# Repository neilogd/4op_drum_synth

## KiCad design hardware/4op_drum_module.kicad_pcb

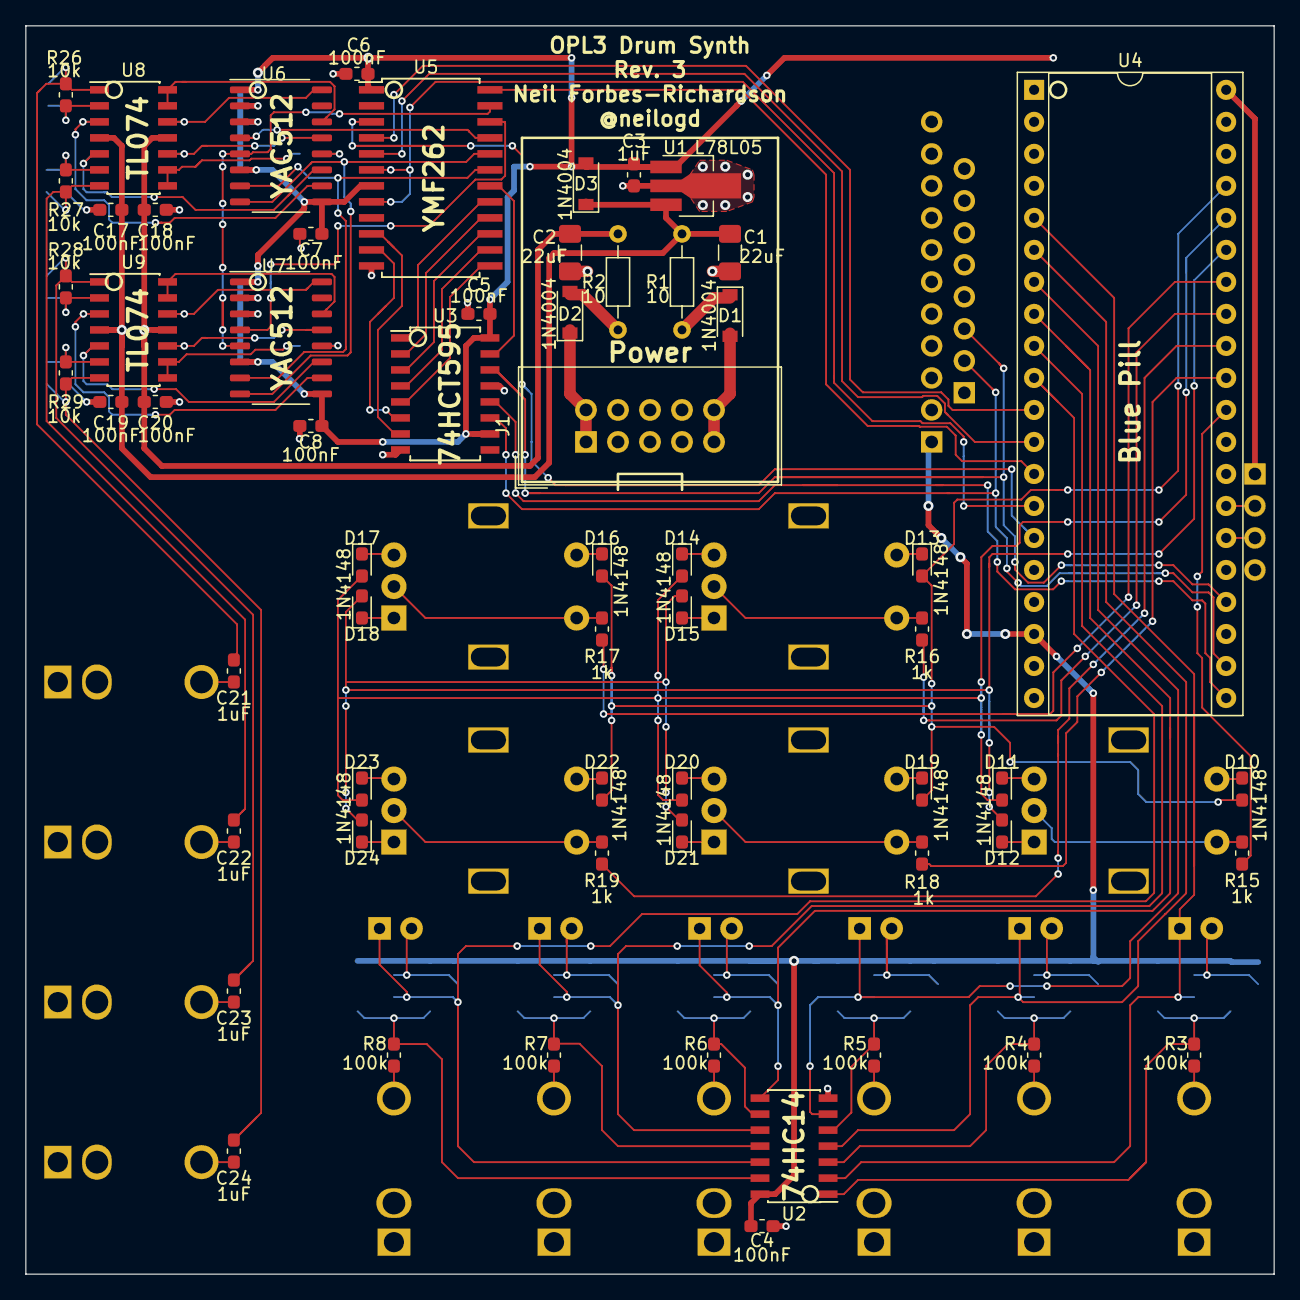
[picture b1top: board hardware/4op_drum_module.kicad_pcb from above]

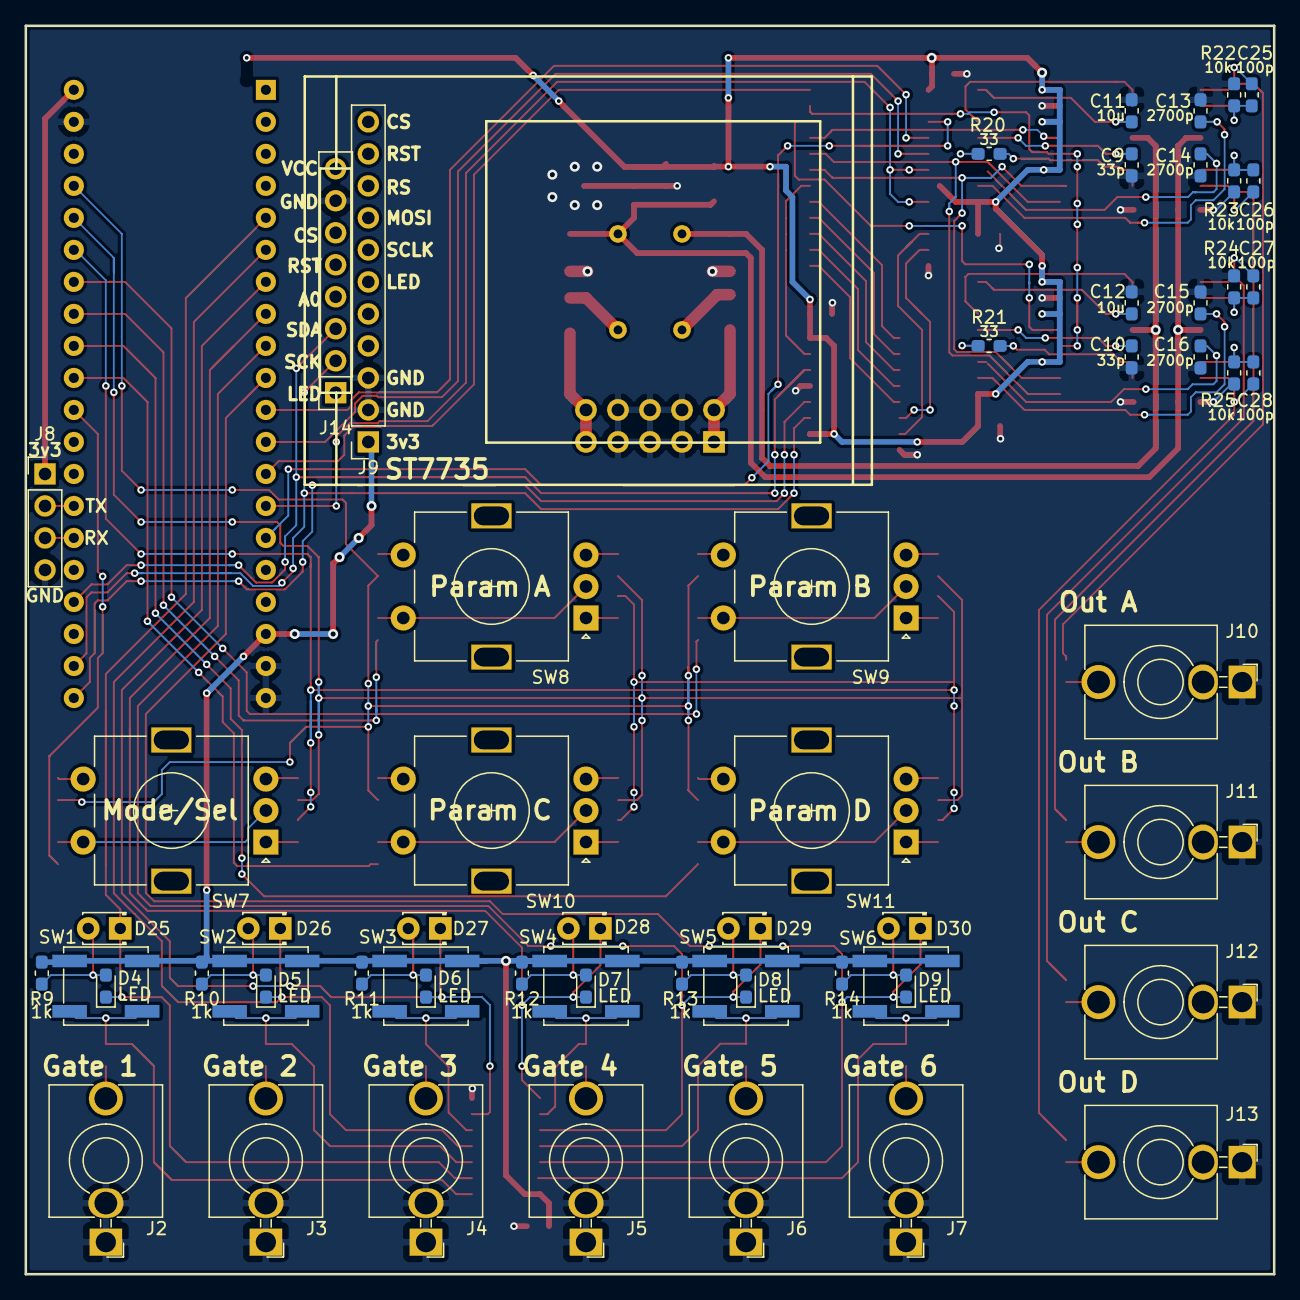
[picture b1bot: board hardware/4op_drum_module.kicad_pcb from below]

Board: 2 copper layers, 99.1 x 99.1 mm, 121 parts (60 on the bottom side), 113 nets.

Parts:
C1, C2: 22uF; C_1206_3216Metric_Pad1.42x1.75mm_HandSolder
C3, C21, C22, C23, C24: 1uF; C_0603_1608Metric_Pad1.05x0.95mm_HandSolder
C4, C5, C6, C7, C8, C17, C18, C19, C20: 100nF; C_0603_1608Metric_Pad1.05x0.95mm_HandSolder
C9, C10: 33p; C_0603_1608Metric_Pad1.05x0.95mm_HandSolder
C11, C12: 10u; C_0603_1608Metric_Pad1.05x0.95mm_HandSolder
C13, C14, C15, C16: 2700p; C_0603_1608Metric_Pad1.05x0.95mm_HandSolder
C25, C26, C27, C28: 100p; C_0603_1608Metric_Pad1.05x0.95mm_HandSolder
D1, D2, D3: 1N4004; D_SOD-123
D4, D5, D6, D7, D8, D9: LED; LED_0603_1608Metric_Pad1.05x0.95mm_HandSolder
D10, D11, D12, D13, D14, D15, D16, D17, D18, D19, D20, D21, D22, D23, D24: 1N4148; D_0603_1608Metric_Pad1.05x0.95mm_HandSolder
D25, D26, D27, D28, D29, D30: LED; LED_D1.8mm_W3.3mm_H2.4mm
J1: Conn_02x05_Eurorack; IDC-Header_2x05_P2.54mm_Vertical
J2, J3, J4, J5, J6, J7, J10, J11, J12, J13: Jack; Jack_3.5mm_QingPu_WQP-PJ398SM_Vertical_CircularHoles_TS
J8: Conn_01x04_Male; PinHeader_1x04_P2.54mm_Vertical
J9: Conn_01x11_Female; PinSocket_1x11_P2.54mm_Vertical
J14: Conn_01x08_Female; PinSocket_1x08_P2.54mm_Vertical
R1, R2: 10; R_Axial_DIN0204_L3.6mm_D1.6mm_P7.62mm_Horizontal
R3, R4, R5, R6, R7, R8: 100k; R_0603_1608Metric_Pad1.05x0.95mm_HandSolder
R9, R10, R11, R12, R13, R14, R15, R16, R17, R18, R19: 1k; R_0603_1608Metric_Pad1.05x0.95mm_HandSolder
R20, R21: 33; R_0603_1608Metric_Pad1.05x0.95mm_HandSolder
R22, R23, R24, R25, R26, R27, R28, R29: 10k; R_0603_1608Metric_Pad1.05x0.95mm_HandSolder
SW1, SW2, SW3, SW4, SW5, SW6: SW_Push; SW_SPST_EVQP0
SW7, SW8, SW9, SW10, SW11: Rotary; RotaryEncoder_Alps_EC11E-Switch_Vertical_H20mm
U1: L78L05; SOT-89-3_Handsoldering
U2: 74HC14; SOIC-14_3.9x8.7mm_P1.27mm
U3: 74HCT595; SOIC-16W_5.3x10.2mm_P1.27mm
U4: BluePill_STM32F103C; DIP-40_W15.24mm_Socket
U5: YMF262; SOIC-24W_7.5x15.4mm_P1.27mm
U6, U7: YAC512; SOIC-16_4.55x10.3mm_P1.27mm
U8, U9: TL074; SOIC-14_3.9x8.7mm_P1.27mm

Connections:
+3V3: C4.1, J8.1, J9.1, J9.6, J14.1, J14.8, R9.1, R10.1, R11.1, R12.1, R13.1, R14.1, SW1.1, SW2.1, SW3.1, SW4.1, SW5.1, SW6.1, U2.14, U4.18, U4.40
+5V: C3.1, C5.1, C6.1, C7.1, C8.1, D3.2, U1.1, U3.10, U3.16, U4.38, U5.1, U5.7, U6.1, U6.3, U6.6, U6.9, U7.1, U7.3, U7.6, U7.9
+12V: C1.1, C17.1, C19.1, D3.1, R1.2, U1.3, U8.4, U9.4
-12V: C2.2, C18.2, C20.2, R2.2, U8.11, U9.11
A0: U4.11, U5.4
A1: U4.12, U5.5
AOUT1: C9.1, U6.13, U8.10
AOUT2: C10.1, U7.13, U9.10
CH1: C13.1, U6.10, U8.3
CH2: C14.1, U6.11, U8.5
CH3: C15.1, U7.10, U9.3
CH4: C16.1, U7.11, U9.5
CLK: U4.13, U5.24
CS: U4.14, U5.6, U5.8
CV1: C11.1, U6.16, U8.12
CV2: C12.1, U7.16, U9.12
D0: U3.7, U5.10
D1: U3.6, U5.11
D2: U3.5, U5.13
D3: U3.4, U5.14
D4: U3.3, U5.15
D5: U3.2, U5.16
D6: U3.1, U5.17
D7: U3.15, U5.18
G0: D4.1, D25.1, U2.2, U4.5
G1: D5.1, D26.1, U2.4, U4.6
G2: D6.1, D27.1, U2.6, U4.7
G3: D7.1, D28.1, U2.8, U4.8
G4: D8.1, D29.1, U2.10, U4.9
G5: D9.1, D30.1, U2.12, U4.10
GND: C1.2, C2.1, C3.2, C4.2, C5.2, C6.2, C7.2, C8.2, C9.2, C10.2, C11.2, C12.2, C13.2, C14.2, C15.2, C16.2, C17.2, C18.1, C19.2, C20.1, J1.3, J1.4, J1.5, J1.6, J1.7, J1.8, J2.1, J2.3, J3.1, J3.3, J4.1, J4.3, J5.1, J5.3, J6.1, J6.3, J7.1, J7.3, J8.4, J9.2, J9.3, J10.1, J11.1, J12.1, J13.1, J14.7, R22.1, R23.1, R24.1, R25.1, U1.2, U2.7, U3.8, U3.13, U4.19, U4.20, U4.39, U5.12, U6.2, U7.2
LED_CS: J9.11, J14.6, U4.2
LED_RS: J9.9, J14.4, U4.4
LED_RST: J9.10, J14.5, U4.3
MOSI: J9.8, J14.3, U3.14, U4.24
MP1: U6.14, U8.13, U8.14
MP2: U7.14, U9.13, U9.14
NSS: U3.12, U4.21
unnamed: C21.1, C25.1, R26.1, U8.1
unnamed: C21.2, J10.2
unnamed: C22.1, C26.1, R27.1, U8.7
unnamed: C22.2, J11.2
unnamed: C23.1, C27.1, R28.2, U9.1
unnamed: C23.2, J12.2
unnamed: C24.1, C28.1, R29.1, U9.7
unnamed: C24.2, J13.2
unnamed: C25.2, R22.2, R26.2, U8.2
unnamed: C26.2, R23.2, R27.2, U8.6
unnamed: C27.2, R24.2, R28.1, U9.2
unnamed: C28.2, R25.2, R29.2, U9.6
unnamed: D1.1, R1.1
unnamed: D1.2, J1.9, J1.10
unnamed: D2.1, J1.1, J1.2
unnamed: D2.2, R2.1
unnamed: D10.1, SW7.S1
unnamed: D11.1, SW7.B
unnamed: D12.1, SW7.A
unnamed: D13.1, SW8.S1
unnamed: D14.1, SW8.B
unnamed: D15.1, SW8.A
unnamed: D16.1, SW9.S1
unnamed: D17.1, SW9.B
unnamed: D18.1, SW9.A
unnamed: D19.1, SW10.S1
unnamed: D20.1, SW10.B
unnamed: D21.1, SW10.A
unnamed: D22.1, SW11.S1
unnamed: D23.1, SW11.B
unnamed: D24.1, SW11.A
unnamed: D4.2, D25.2, R9.2
unnamed: D5.2, D26.2, R10.2
unnamed: D6.2, D27.2, R11.2
unnamed: D7.2, D28.2, R12.2
unnamed: D8.2, D29.2, R13.2
unnamed: D9.2, D30.2, R14.2
unnamed: J2.2, R3.1
unnamed: J3.2, R4.1
unnamed: J4.2, R5.1
unnamed: J5.2, R6.1
unnamed: J6.2, R7.1
unnamed: J7.2, R8.1
unnamed: J8.2, U4.27
unnamed: J8.3, U4.26
unnamed: R3.2, SW1.2, U2.1
unnamed: R4.2, SW2.2, U2.3
unnamed: R5.2, SW3.2, U2.5
unnamed: R6.2, SW4.2, U2.9
unnamed: R7.2, SW5.2, U2.11
unnamed: R8.2, SW6.2, U2.13
unnamed: R15.1, SW7.C, SW7.S2
unnamed: R16.1, SW8.C, SW8.S2
unnamed: R17.1, SW9.C, SW9.S2
unnamed: R18.1, SW10.C, SW10.S2
unnamed: R19.1, SW11.C, SW11.S2
unnamed: R20.2, U6.12
unnamed: R21.2, U7.12
unnamed: U5.19, U6.7, U7.7
unnamed: U5.20, U6.8, U7.8
unnamed: U5.21, U6.4
unnamed: U5.22, U7.4
unnamed: U5.23, U6.5, U7.5
RST: U4.15, U5.3
R_C0: R15.2, U4.30
R_C1: R16.2, U4.33
R_C2: R17.2, U4.34
R_C3: R18.2, U4.31
R_C4: R19.2, U4.32
R_R0: D11.2, D14.2, D17.2, D20.2, D23.2, U4.36
R_R1: D12.2, D15.2, D18.2, D21.2, D24.2, U4.35
R_R2: D10.2, D13.2, D16.2, D19.2, D22.2, U4.37
SCLK: J9.7, J14.2, U3.11, U4.22
SWIN1: R20.1, U8.8, U8.9
SWIN2: R21.1, U9.8, U9.9

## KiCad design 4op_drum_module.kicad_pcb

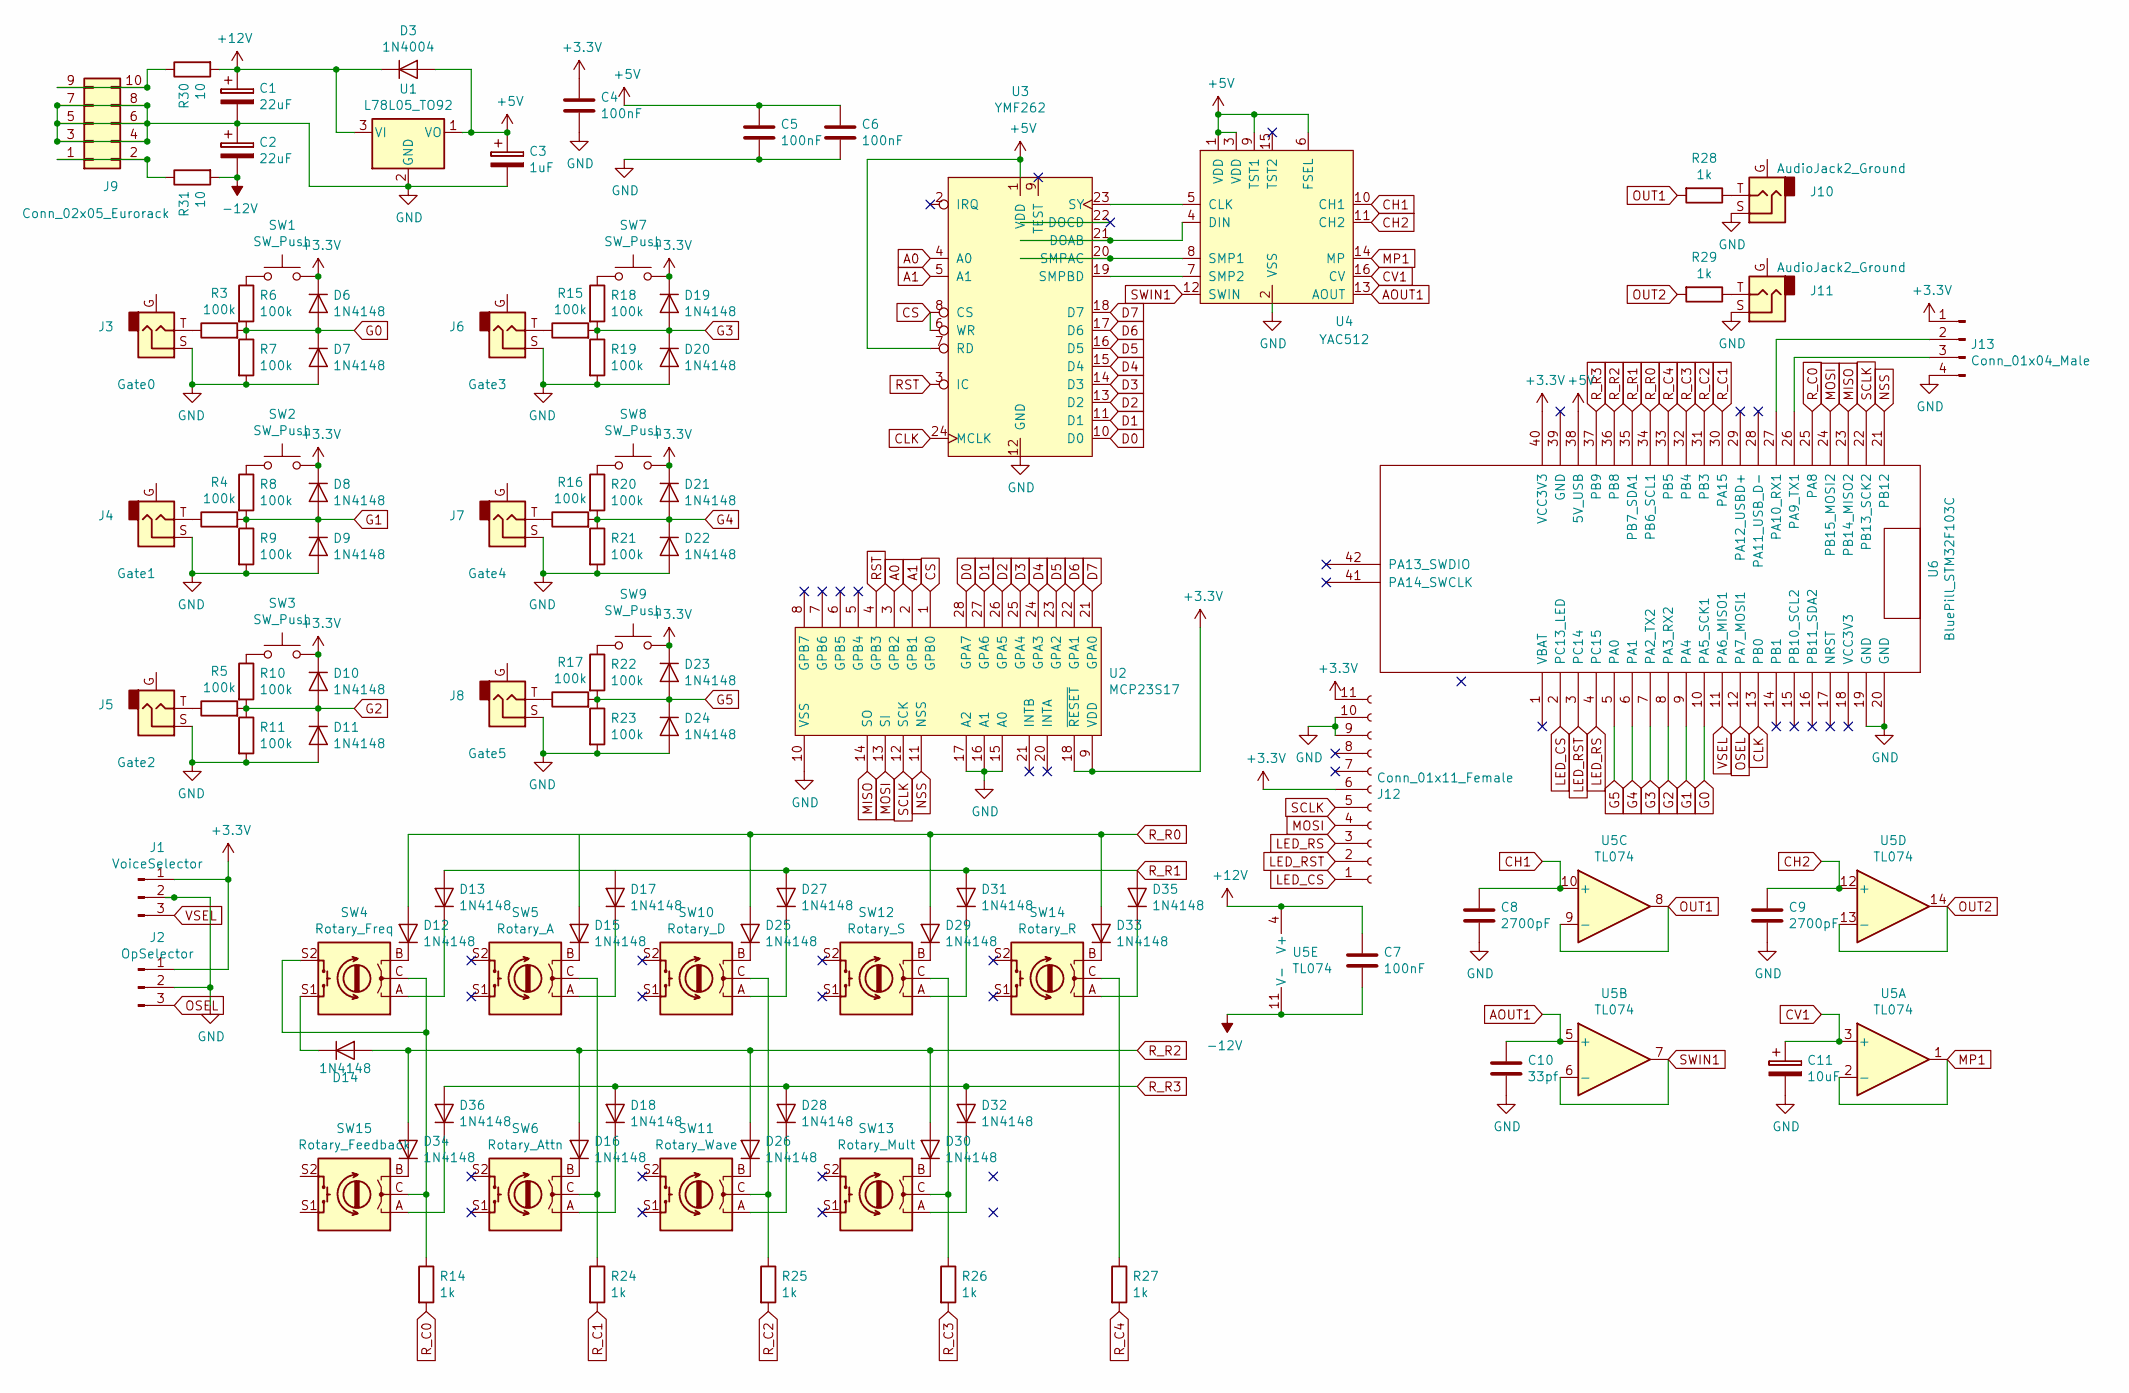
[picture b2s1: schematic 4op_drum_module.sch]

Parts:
C1, C2: 22uF; CP_Radial_D4.0mm_P2.00mm
C3: 1uF; CP_Radial_D4.0mm_P2.00mm
C4, C5, C6: 100nF; C_0603_1608Metric_Pad1.05x0.95mm_HandSolder
C7: 100nF; C_Disc_D5.0mm_W2.5mm_P5.00mm
C8, C9: 2700pF; C_0603_1608Metric_Pad1.05x0.95mm_HandSolder
C10: 33pf; C_0603_1608Metric_Pad1.05x0.95mm_HandSolder
C11: 10uF; CP_Radial_D5.0mm_P2.50mm
D3: 1N4004; D_DO-34_SOD68_P2.54mm_Vertical_AnodeUp
D6, D7, D8, D9, D10, D11, D12, D13, D14, D15, D16, D17, D18, D19, D20, D21, D22, D23, D24, D25, D26, D27, D28, D29, D30, D31, D32, D33, D34, D35, D36: 1N4148; D_DO-35_SOD27_P2.54mm_Vertical_AnodeUp
J1: VoiceSelector; PinHeader_1x03_P2.54mm_Vertical
J2: OpSelector; PinHeader_1x03_P2.54mm_Vertical
J3: Gate0; Jack_3.5mm_QingPu_WQP-PJ398SM_Vertical_CircularHoles_TS
J4: Gate1; Jack_3.5mm_QingPu_WQP-PJ398SM_Vertical_CircularHoles_TS
J5: Gate2; Jack_3.5mm_QingPu_WQP-PJ398SM_Vertical_CircularHoles_TS
J6: Gate3; Jack_3.5mm_QingPu_WQP-PJ398SM_Vertical_CircularHoles_TS
J7: Gate4; Jack_3.5mm_QingPu_WQP-PJ398SM_Vertical_CircularHoles_TS
J8: Gate5; Jack_3.5mm_QingPu_WQP-PJ398SM_Vertical_CircularHoles_TS
J9: Conn_02x05_Eurorack; PinHeader_2x05_P2.54mm_Vertical
J10, J11: AudioJack2_Ground; Jack_3.5mm_QingPu_WQP-PJ398SM_Vertical_CircularHoles_TS
J12: Conn_01x11_Female; PinSocket_1x11_P2.54mm_Vertical
J13: Conn_01x04_Male; PinHeader_1x04_P2.54mm_Vertical
R3, R4, R5, R6, R7, R8, R9, R10, R11, R15, R16, R17, R18, R19, R20, R21, R22, R23: 100k; R_0603_1608Metric_Pad1.05x0.95mm_HandSolder
R14, R24, R25, R26, R27, R28, R29: 1k; R_0603_1608Metric_Pad1.05x0.95mm_HandSolder
R30, R31: 10; R_Axial_DIN0204_L3.6mm_D1.6mm_P7.62mm_Horizontal
SW1, SW2, SW3, SW7, SW8, SW9: SW_Push; PinHeader_1x02_P2.54mm_Vertical
SW4: Rotary_Freq; RotaryEncoder_Alps_EC11E-Switch_Vertical_H20mm
SW5: Rotary_A; RotaryEncoder_Alps_EC11E-Switch_Vertical_H20mm
SW6: Rotary_Attn; RotaryEncoder_Alps_EC11E-Switch_Vertical_H20mm
SW10: Rotary_D; RotaryEncoder_Alps_EC11E-Switch_Vertical_H20mm
SW11: Rotary_Wave; RotaryEncoder_Alps_EC11E-Switch_Vertical_H20mm
SW12: Rotary_S; RotaryEncoder_Alps_EC11E-Switch_Vertical_H20mm
SW13: Rotary_Mult; RotaryEncoder_Alps_EC11E-Switch_Vertical_H20mm
SW14: Rotary_R; RotaryEncoder_Alps_EC11E-Switch_Vertical_H20mm
SW15: Rotary_Feedback; RotaryEncoder_Alps_EC11E-Switch_Vertical_H20mm
U1: L78L05_TO92; TO-92_Inline
U2: MCP23S17; DIP-28_W7.62mm_Socket
U3: YMF262; SOIC-24W_7.5x15.4mm_P1.27mm
U4: YAC512; SOIC-16_4.55x10.3mm_P1.27mm
U5: TL074; DIP-14_W7.62mm
U6: BluePill_STM32F103C; DIP-40_W15.24mm_Socket

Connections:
+3V3: C4.1, D6.1 (K), D8.1 (K), D10.1 (K), D19.1 (K), D21.1 (K), D23.1 (K), J1.1, J2.1, J12.6, J12.11, J13.1, SW1.2, SW2.2, SW3.2, SW7.2, SW8.2, SW9.2, U2.9 (VDD), U2.18 (~RESET), U6.40 (VCC3V3)
+5V: C3.1, C5.1, C6.1, D3.2 (A), U1.1 (VO), U3.1 (VDD), U3.7 (RD), U4.1 (VDD), U4.3 (VDD), U4.6 (FSEL), U4.9 (TST1), U6.38 (5V_USB)
+12V: C1.1, C7.1, D3.1 (K), R30.2, U1.3 (VI), U5.4 (V+)
-12V: C2.2, C7.2, R31.2, U5.11 (V-)
A0: U2.3 (GPB2), U3.4 (A0)
A1: U2.2 (GPB1), U3.5 (A1)
AOUT1: C10.1, U4.13 (AOUT), U5.5 (+)
CH1: C8.1, U4.10 (CH1), U5.10 (+)
CH2: C9.1, U4.11 (CH2), U5.12 (+)
CLK: U3.24 (MCLK), U6.13 (PB0)
CS: U2.1 (GPB0), U3.6 (WR), U3.8 (CS)
CV1: C11.1, U4.16 (CV), U5.3 (+)
D0: U2.28 (GPA7), U3.10 (D0)
D1: U2.27 (GPA6), U3.11 (D1)
D2: U2.26 (GPA5), U3.13 (D2)
D3: U2.25 (GPA4), U3.14 (D3)
D4: U2.24 (GPA3), U3.15 (D4)
D5: U2.23 (GPA2), U3.16 (D5)
D6: U2.22 (GPA1), U3.17 (D6)
D7: U2.21 (GPA0), U3.18 (D7)
G0: D6.2 (A), D7.1 (K), R3.2, R6.2, R7.1, U6.10 (PA5_SCK1)
G1: D8.2 (A), D9.1 (K), R4.2, R8.2, R9.1, U6.9 (PA4)
G2: D10.2 (A), D11.1 (K), R5.2, R10.2, R11.1, U6.8 (PA3_RX2)
G3: D19.2 (A), D20.1 (K), R15.2, R18.2, R19.1, U6.7 (PA2_TX2)
G4: D21.2 (A), D22.1 (K), R16.2, R20.2, R21.1, U6.6 (PA1)
G5: D23.2 (A), D24.1 (K), R17.2, R22.2, R23.1, U6.5 (PA0)
GND: C1.2, C2.1, C3.2, C4.2, C5.2, C6.2, C8.2, C9.2, C10.2, C11.2, D7.2 (A), D9.2 (A), D11.2 (A), D20.2 (A), D22.2 (A), D24.2 (A), J1.2, J2.2, J3.S, J4.S, J5.S, J6.S, J7.S, J8.S, J9.3, J9.4, J9.5, J9.6 (ePin_6), J9.7, J9.8, J10.S, J11.S, J12.9, J12.10, J13.4, R7.2, R9.2, R11.2, R19.2, R21.2, R23.2, U1.2 (GND), U2.10 (VSS), U2.15 (A0), U2.16 (A1), U2.17 (A2), U3.12 (GND), U4.2 (VSS), U6.19 (GND), U6.20 (GND)
LED_CS: J12.1, U6.2 (PC13_LED)
LED_RS: J12.3, U6.4 (PC15)
LED_RST: J12.2, U6.3 (PC14)
MISO: U2.14 (SO), U6.23 (PB14_MISO2)
MOSI: J12.4, U2.13 (SI), U6.24 (PB15_MOSI2)
MP1: U4.14 (MP), U5.1, U5.2 (-)
NSS: U2.11 (NSS), U6.21 (PB12)
unnamed: D12.1 (K), SW4.B
unnamed: D13.1 (K), SW4.A
unnamed: D14.1 (K), SW4.S1
unnamed: D15.1 (K), SW5.B
unnamed: D16.1 (K), SW6.B
unnamed: D17.1 (K), SW5.A
unnamed: D18.1 (K), SW6.A
unnamed: D25.1 (K), SW10.B
unnamed: D26.1 (K), SW11.B
unnamed: D27.1 (K), SW10.A
unnamed: D28.1 (K), SW11.A
unnamed: D29.1 (K), SW12.B
unnamed: D30.1 (K), SW13.B
unnamed: D31.1 (K), SW12.A
unnamed: D32.1 (K), SW13.A
unnamed: D33.1 (K), SW14.B
unnamed: D34.1 (K), SW15.B
unnamed: D35.1 (K), SW14.A
unnamed: D36.1 (K), SW15.A
unnamed: J3.T, R3.1
unnamed: J4.T, R4.1
unnamed: J5.T, R5.1
unnamed: J6.T, R15.1
unnamed: J7.T, R16.1
unnamed: J8.T, R17.1
unnamed: J9.1, J9.2, R31.1
unnamed: J9.9, J9.10, R30.1
unnamed: J10.T, R28.1
unnamed: J11.T, R29.1
unnamed: J13.2, U6.27 (PA10_RX1)
unnamed: J13.3, U6.26 (PA9_TX1)
unnamed: R6.1, SW1.1
unnamed: R8.1, SW2.1
unnamed: R10.1, SW3.1
unnamed: R14.1, SW4.C, SW4.S2, SW15.C
unnamed: R18.1, SW7.1
unnamed: R20.1, SW8.1
unnamed: R22.1, SW9.1
unnamed: R24.1, SW5.C, SW6.C
unnamed: R25.1, SW10.C, SW11.C
unnamed: R26.1, SW12.C, SW13.C
unnamed: R27.1, SW14.C
unnamed: U3.19 (SMPBD), U4.7 (SMP2)
unnamed: U3.20 (SMPAC), U4.8 (SMP1)
unnamed: U3.21 (DOAB), U4.4 (DIN)
unnamed: U3.23 (SY), U4.5 (CLK)
OSEL: J2.3, U6.12 (PA7_MOSI1)
OUT1: R28.2, U5.8, U5.9 (-)
OUT2: R29.2, U5.13 (-), U5.14
RST: U2.4 (GPB3), U3.3 (IC)
R_C0: R14.2, U6.25 (PA8)
R_C1: R24.2, U6.30 (PA15)
R_C2: R25.2, U6.31 (PB3)
R_C3: R26.2, U6.32 (PB4)
R_C4: R27.2, U6.33 (PB5)
R_R0: D12.2 (A), D15.2 (A), D25.2 (A), D29.2 (A), D33.2 (A), U6.34 (PB6_SCL1)
R_R1: D13.2 (A), D17.2 (A), D27.2 (A), D31.2 (A), D35.2 (A), U6.35 (PB7_SDA1)
R_R2: D14.2 (A), D16.2 (A), D26.2 (A), D30.2 (A), D34.2 (A), U6.36 (PB8)
R_R3: D18.2 (A), D28.2 (A), D32.2 (A), D36.2 (A), U6.37 (PB9)
SCLK: J12.5, U2.12 (SCK), U6.22 (PB13_SCK2)
SWIN1: U4.12 (SWIN), U5.6 (-), U5.7
VSEL: J1.3, U6.11 (PA6_MISO1)

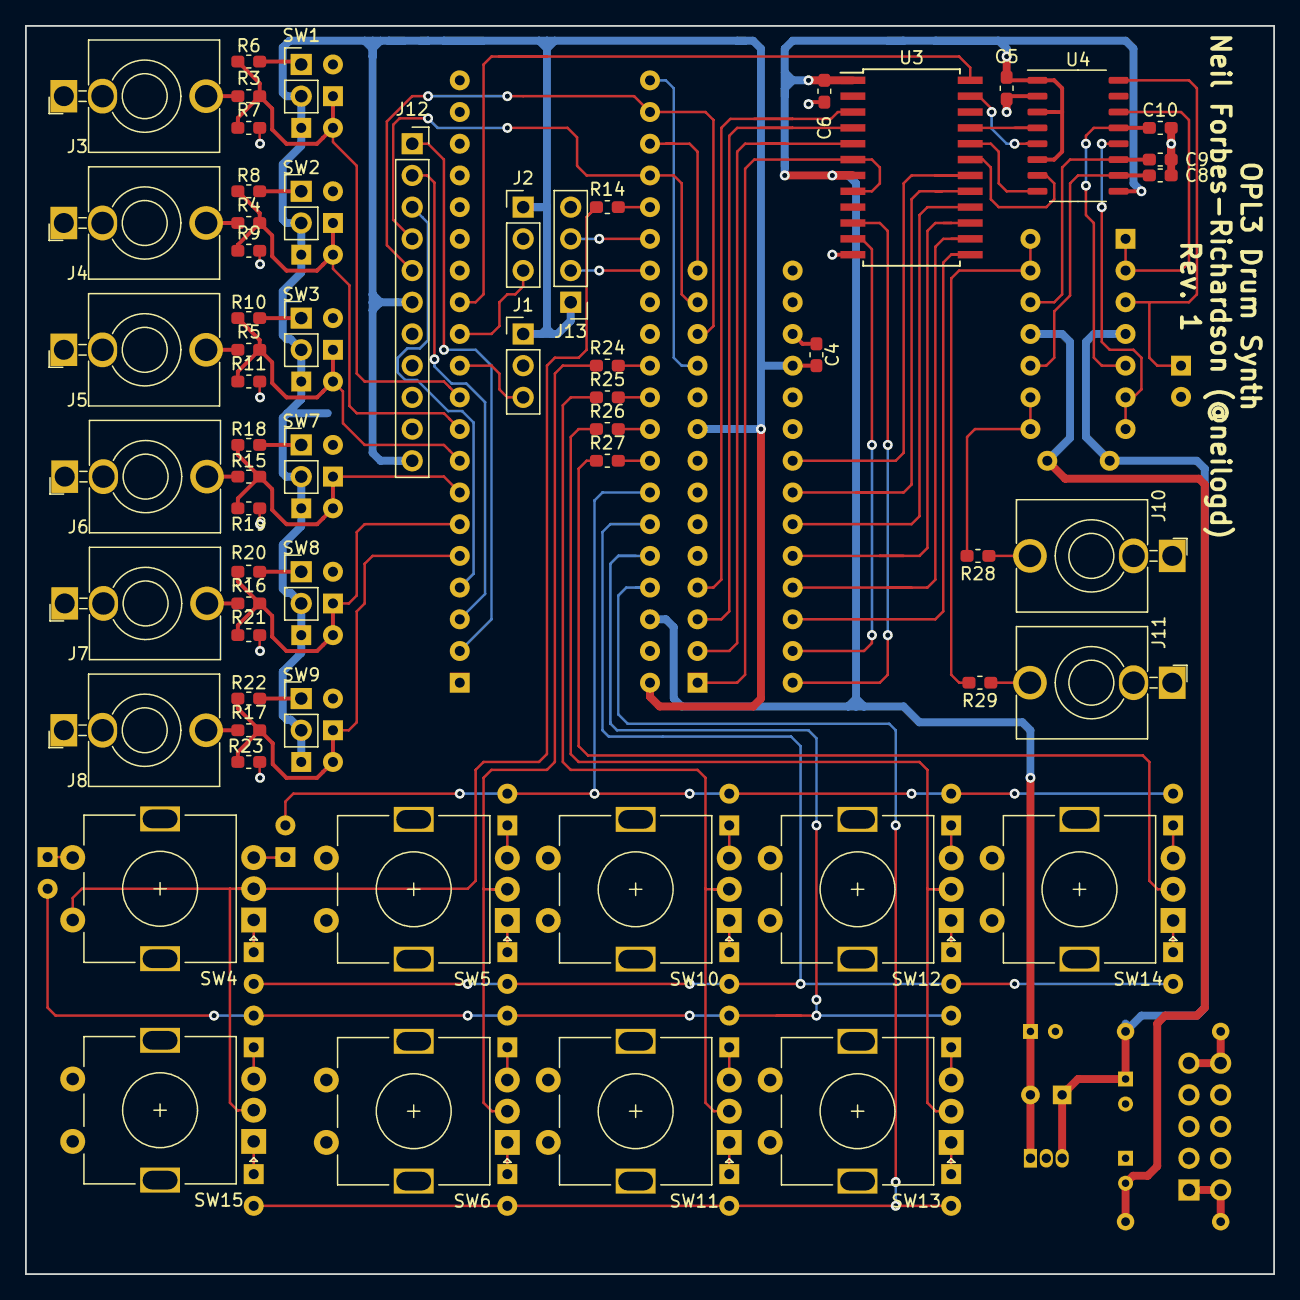
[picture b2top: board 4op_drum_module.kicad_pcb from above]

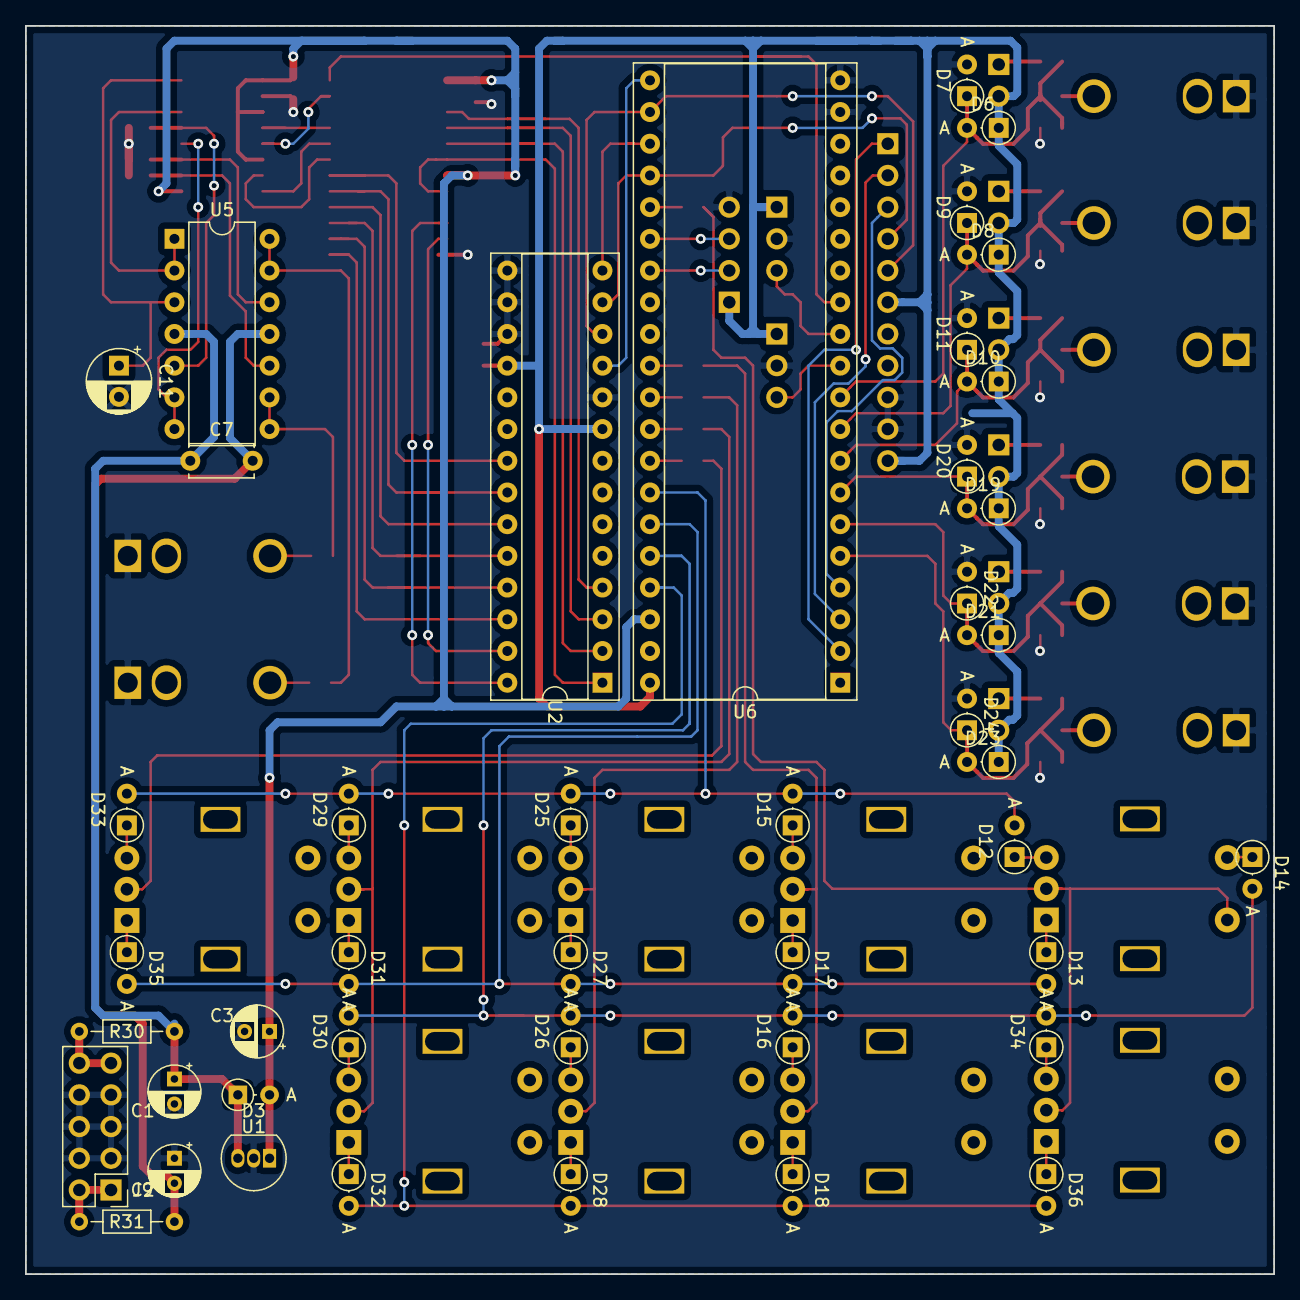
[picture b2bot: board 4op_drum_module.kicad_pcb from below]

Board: 2 copper layers, 100.0 x 100.0 mm, 104 parts (44 on the bottom side), 96 nets.

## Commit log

2019-01-21 Initisal commit.
2019-01-23 Added MIDI SysEx stuff
2019-01-24 Move source code into firmware folder, begin tidying up code
2019-01-24 Encoder and button config moved into config.h
2019-01-24 Moved colors into config.h
2019-01-24 Moved some things out of firmware.ino, minor tidy up
2019-01-24 pow->powf, add embedded printf. Reduces binary size significantly
2019-01-24 gate more sensitive, powf fast added, but unused due to precision issues (need to look at it again)
2019-01-26 Configurable rotary encoder position
2019-01-27 Added MIDI input support so it can be driven via MIDI channel 1-6, and channel 10.
2019-09-03 Big refactoring of the firmware.
2019-09-03 Stripped out old junk, added ctrlr panel (still todo)
2019-09-03 Moved kicad stuff into hardware folder
2019-09-03 Updated gfx library
2019-09-04 Added binary size dumping when building STM32
2019-09-04 Channel selection added to voice, few other small bits
2019-09-04 Remove build junk, setup gitignore
